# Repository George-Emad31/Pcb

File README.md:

# Pcb
course links

—-----------------------------------------------------------
An Introductory Session to the field & market by Eng. Marina & Abdelrahman
https://youtu.be/WNl0apc1B7U?si=2tqRJhkXzuk2Huat
—-----------------------------------------------------------
وليد عيسي
١- دورة الالكترونيات العملية 
https://youtube.com/playlist?list=PLww54WQ2wa5rOJ7FcXxi-CMNgmpybv7ei&si=CNx4IFHqYKsxTS9Y

٢- دورة الالكترونيات الرقمية 
https://youtube.com/playlist?list=PLww54WQ2wa5obq6IbRbIiql8oHaTUp3T_&si=EiO0YVdOyis6UTqZ

١- و ٢- ممكن تستبدلهم ب
(crash course electronics & PCB Design)
علي (Udemy) ل Andre Lamothe 👇

https://www.udemy.com/course/crash-course-electronics-and-pcb-design/?couponCode=SKILLS4SALEB

٣- دورة التصميم الالكتروني المحترف
https://youtube.com/playlist?list=PLww54WQ2wa5oKEhE_D3UVbKWwml8o8_Fu&si=GUjIskn36xYq0Vrd
 
٤- باور الكترونكس
https://youtube.com/playlist?list=PLa7G9a0g8LGJGPSlsJ-3jR8Icn2ZBpkbO&si=j0Y4SN-4wLoZTFAJ

٥-  في المختبر 
https://youtube.com/playlist?list=PLww54WQ2wa5oE2p9IJzItQwpLKtizHO_H&si=7gjoG86Fukzq-uNG

Dr.Mohamed Youssef (PCB Basics)
https://youtube.com/playlist?list=PLfgCIULRQavx6TjOhr_7pkx7ne4kI1r2N
Walid Balid (PCB Basics)
https://youtube.com/playlist?list=PL_UUr-UkFMWRXeJ2mKt5jidU5hId4-gwY&si=ZF-LGmuCmhe2fAAh

م.عمرو عباس (Altium)  
https://youtube.com/playlist?list=PLjAwsXyLubqXhIs1Xjf421pyehGvs9RpD&si=hDhPsAw99uElP_TQ

د.محمد الشامي  (Altium) 
https://youtube.com/playlist?list=PLZ42ZUInDWC5hSe0zNn84jiYI7bpQkXqb&si=qIUQ1LDYL5tfv7yA

Shawn Hymel (Kicad)
https://youtube.com/playlist?list=PL3bNyZYHcRSUhUXUt51W6nKvxx2ORvUQB&feature=shared

Parallel Systems EDA (OrCAD Allegro)
https://www.youtube.com/@parsysEDA/videos

Andre Lamothe (Embedded)
(Crash Course Arduino and Microcontroller Development)
https://www.udemy.com/course/crash-course-arduino-and-microcontroller-development/?couponCode=SKILLS4SALEB

Another Recommended good Embedded Course 
https://www.udemy.com/course/microcontrollers-sensors-actuators-recorded-by-arabic/?couponCode=SKILLS4SALEB
______________________________________

FastBit Embedded Brain Academy Embedded
https://www.udemy.com/user/kiran-nayak-2/?kw=Fastbit&src=sac

Robert Feranec     (YouTube channel + 3 paid courses)
https://www.youtube.com/@RobertFeranec

- learn to design your own board (Udemy)
- Advanced hardware design (fedevel academy)
- Advanced PCB layout (fedevel academy)
https://www.udemy.com/share/1029yK3@ESy1HsZxC51XGr01DA7xO2LyQJOntExK32Gf5kavSXH6ODqpkA5D4g6xnz0SwEeq7w==/

https://www.fedevel.com/courses

Phil's lab (YouTube channel + 2 paid courses)
https://www.youtube.com/@PhilsLab

- Mixed signal hardware design (fedevel academy)
- Advanced digital hardware design (fedevel academy)
https://www.fedevel.com/courses
______________________________________________________________________________
Eric Bogatin Academy
https://teledynelecroy.bethesignal.com/pages/24/signal-integrity-academy-be-the-signal

Altium Academy
https://www.youtube.com/@AltiumAcademy

EsteemPCB academy (YouTube + 4 Udemy courses)
https://www.youtube.com/@EsteemPCB
https://www.udemy.com/user/aviral-mishra-37/

STM32 IOT LTE Hardware Design course (Udemy)
https://www.udemy.com/course/stm32-internet-of-things-with-4g-lte-modem-hardware/

Hans Rosenberg (RF PCB Layout)
https://www.youtube.com/@HansRosenberg74
______________________________________________________________________________
RAHsoft courses (RF + Communication + Antenna)
https://www.udemy.com/user/rahsoft-rf-certificate/
https://www.udemy.com/user/security-and-cryptography-rahsoft-cyber-certificate/
______________________________________________________________________________
Kirsch Mackey (Hasofu Academy) 
https://youtube.com/@techedkirsch?si=i_7RqJdtHQidq5RQ

https://academy.hasofu.com/course/hardware-engineer-accelerator-videos-group
______________________________________________________________________________
Microchip University Courses 
https://mu.microchip.com/page/all-courses

Dario Fresu   (YouTube + Skool Academy website and application)  (Content related to EMC)
https://www.youtube.com/@dario_fresu
https://kp.odysee.tv/@fresudario:3?view=content
____________________________________________________________________________
Karen Burnham (EMC Basics)
https://www.udemy.com/course/emc-engineering-basics/?kw=emc+engineering&src=sac

Technologies Discussion (EMC course)
https://youtube.com/playlist?list=PLFxhgwM1F4ywicEggR3pzF0FcFcGQvZ82&si=Gw-rwGJun5NXbTx-

EMC Academy 
https://www.academyofemc.com/

Learn EMC
https://learnemc.com/

Keith Armstrong (EMC courses)
https://fedevel.com/instructors/keith-armstrong
_____________________________________________________________________
Ninedotconnects (High-Speed & Signal Integrity)
https://www.ninedotconnects.com/video-high-speed-design

Practical High-Speed Digital Design
https://www.udemy.com/course/practical-high-speed-digital-design/?couponCode=KEEPLEARNING
—-----------------------------------------------------------------------------------------------------------------------------
PCB/Electronics: Thermal Management, Cooling and Derating
https://www.udemy.com/course/pcbelectronics-thermal-management-derating-fundamentals/?kw=thermal+manag&src=sac&couponCode=KEEPLEARNING
—-------------------------------------------------------------------------------------------------------------------------
Battery Management Systems Specialization   (Coursera)
https://www.coursera.org/specializations/algorithms-for-battery-management-systems
BMS material by Colorado Boulder university
https://mocha-java.uccs.edu/ECE5720/index.html
http://mocha-java.uccs.edu/
BMS courses (Udemy)
https://www.udemy.com/user/ritul-shah/
—-----------------------------------------------------------
Microcontroller + Digital Control + Python for Power Electronics
https://www.udemy.com/user/shivkumar-iyer/
—-------------------------------------------------------------------------------------------------------------------------
- Power Electronics Specialization  (Coursera)
https://www.coursera.org/specializations/power-electronics

*MIT University Power Electronics Lectures*
Lectures
https://youtube.com/playlist?list=PLUl4u3cNGP62UTc77mJoubhDELSC8lfR0&si=k29GKX0zg4WzzoGR
Written, Quizzes 
https://ocw.mit.edu/courses/6-622-power-electronics-spring-2023/pages/syllabus/
—-----------------------------------------------------------------------------------------------------------------------------
Flyback Converter Design
https://www.youtube.com/@electrokickoff/playlists
—-----------------------------------------------------------------------------------------------------------------------------
AC/DC-DC Converters course by Eng.Islam Saeed
https://youtu.be/kJaOMY92Ivg?si=VJFJQ_Acn8bhjlOw
https://www.linkedin.com/posts/islamsaeedrej_smps-design-course-online-activity-7283790675265867777-NSWV?utm_source=share&utm_medium=member_desktop&rcm=ACoAAC2EX84B1PiRTD7OQLJM88wBkoDjDiXYB1M

HW Engineer to the Market course by Eng.Islam Saeed
https://www.linkedin.com/posts/islamsaeedrej_hwabrengineerabrtoabrmarket-hw-electronics-activity-7241157567031222272-e6iD?utm_source=share&utm_medium=member_desktop&rcm=ACoAAC2EX84B1PiRTD7OQLJM88wBkoDjDiXYB1M

Eng.Fahd Fakhry (3 Udemy Courses)
- Voltage control DC-DC Converters
- Current control DC-DC Converters
- Motor Control
https://www.udemy.com/user/fahd-fakhry/
  
Sam Ben Yaakov
https://youtube.com/@sambenyaakov?si=wgDwYokDsXTC1p-A

LTspice Simulator
https://youtube.com/playlist?list=PLT84nve2j1g_wgGcm0Bv3K4RSl2Jdjsey&si=4YQyyxi4m5Yk-7JN
https://www.youtube.com/@MarcosAlonsoElectronics
https://www.udemy.com/course/ltspice-tutorial-for-beginners/?srsltid=AfmBOopKCXsha7NvuIdynjStsrGotg1k3i8vl-c6bjZIeW8euqYZ-T-9&couponCode=KEEPLEARNING
-Springer book is very detailed & suitable for beginners (In books folder)

Hardware Design Diploma by Eng. Mahmoud Arafa 
https://www.linkedin.com/posts/mahmoud-arafa-63b1531a2_%D9%88%D9%85%D8%A7-%D8%A3%D9%88%D8%AA%D9%8A%D8%AA%D9%85-%D9%85%D9%86-%D8%A7%D9%84%D8%B9%D9%84%D9%85-%D8%A5%D9%84%D8%A7-activity-7301257242983444480-LV6l?utm_source=share&utm_medium=member_android&rcm=ACoAAC2EX84B1PiRTD7OQLJM88wBkoDjDiXYB1M
—-----------------------------------------------------------------------------------------------------------------------------
FPGA & ASIC & Digital Design Roadmap+Courses

https://github.com/m3y54m/FPGA-ASIC-Roadmap
https://docs.google.com/document/d/10o4X9itOy4x89zeV04_ipY3Gark36JPEXNdBuAvmYeo/edit?usp=drivesdk

https://www.coursera.org/specializations/fpga-design

https://www.udemy.com/course/learn-fpga-design-with-vhdl/?couponCode=KEEPLEARNING

https://www.udemy.com/user/scott-dickson-24/
—-----------------------------------------------------------------------------------------------------------------------------

Valuable Youtube Channels/Webinars

(Rick Hartley) (Grounding)
https://www.youtube.com/live/ySuUZEjARPY?si=bUzMwo6jEBJyy3bA
Kenneth Wyatt (EMC)
https://youtu.be/Krz2Ylj1ZL0?si=EmpSjO_qbGCL12Qk

(Switching Power Supply PCB Layout seminar)
https://www.youtube.com/watch?v=gq-0ZpcGm8E&list=PL5HT7zybEW4T6YcbzQNgPOsIHYw9Rx3MO&index=1&t=1s

https://youtube.com/@electronicmindsuk?si=DOjJMiWhiH3QeP5y

https://www.youtube.com/@DeepBlueMbedded/video

https://www.youtube.com/watch?v=Rgaq5ax71fE&t=1924s

https://youtu.be/cp7II9eqrRU?si=URyDxuNK9eS4KUwh

https://youtube.com/@protoexpresspcb?si=lShLU8rDZzs9lSuV

https://www.youtube.com/live/ySuUZEjARPY?si=1zLlpm-SNm39GcgB

https://www.youtube.com/@electrokickoff

https://www.youtube.com/@AbdelrahmanFarghly/videos

https://www.youtube.com/@mehdiferdowsi9085/videos

https://youtube.com/@techedkirschee?si=Nm_miLClPOZQhHhi

https://youtube.com/@myvanitar?si=56ywRsskvA4lR-qZ

https://www.youtube.com/@EEVblog

https://www.youtube.com/@ELECTRONOOBS

https://www.youtube.com/@greatscottlab

https://www.youtube.com/@BenEater

https://youtube.com/@allaboutelectronics?si=6oBa0x1gGjo1Kh3a

https://www.youtube.com/@0033mer

https://youtube.com/@pcbafrica?si=ll_wLASnqxahkNoS

https://youtube.com/@wuerthelektronikindia-syst5575?si=KUmm86rngWClG2IF

https://youtube.com/@birichalectures?si=rNIujXQz3ECKQT6f

https://youtube.com/@machonedesignemc?si=mH5KCG_DfA04g-Ms

https://youtube.com/@rohde-schwarz?si=MPC_WLR9FluGZkrc

https://youtube.com/@brianbdouglas?si=jIRKR843M4sZlig2

https://youtu.be/HTywk_tlcAk?si=R28jWKTjXR82VGE_

https://www.youtube.com/@pantechelearning

https://youtube.com/@manoa98a?si=2GIbcFX2UrzrGINO

https://youtube.com/@electrobuff?si=7wJEBCNmq7W81LR6

https://youtube.com/@electronicscircuithubech?si=H3kTSfEw0ztwP0nA

https://youtube.com/@technologiesdiscussion1676?si=lvN-GNv7xp8e9dRu

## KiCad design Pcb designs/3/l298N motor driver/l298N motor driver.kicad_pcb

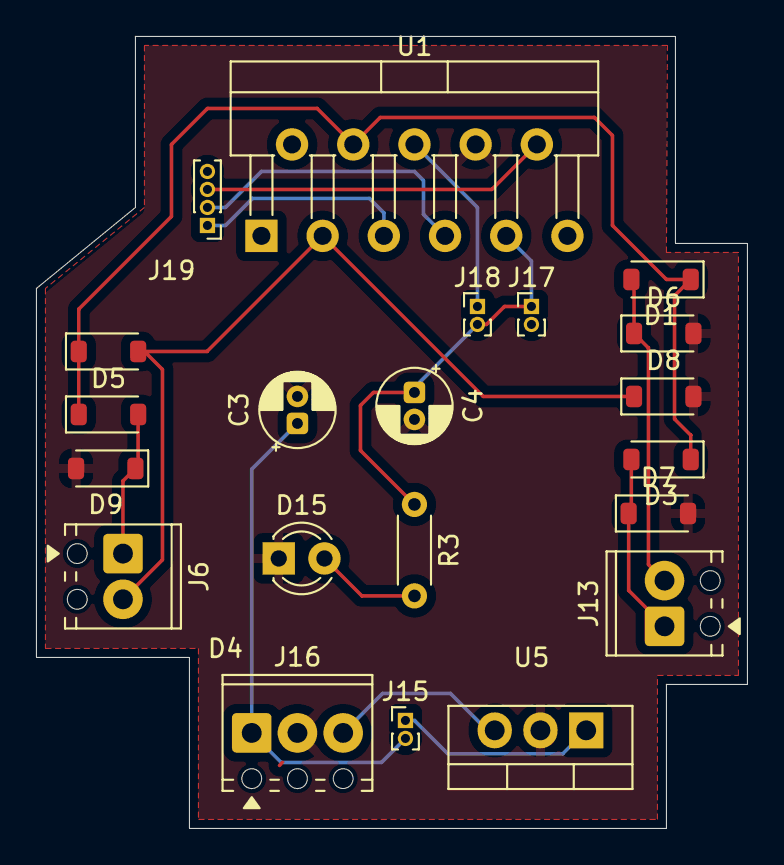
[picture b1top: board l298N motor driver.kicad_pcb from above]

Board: 2 copper layers, 39.5 x 44.0 mm, 21 parts (0 on the bottom side), 15 nets.

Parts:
C3, C4: C_Polarized_Small; CP_Radial_D4.0mm_P1.50mm
D1, D3, D4, D5, D6, D7, D8, D9: BAV16W; D_SOD-123
D15: LED; LED_D3.0mm
J6, J13: Screw_Terminal_01x02; TerminalBlock_Phoenix_MPT-0,5-2-2.54_1x02_P2.54mm_Horizontal
J15, J17, J18: Conn_01x02_Pin; PinHeader_1x02_P1.00mm_Vertical
J16: Screw_Terminal_01x03; TerminalBlock_Phoenix_MPT-0,5-3-2.54_1x03_P2.54mm_Horizontal
J19: Conn_01x04_Pin; PinHeader_1x04_P1.00mm_Vertical
R3: R; R_Axial_DIN0204_L3.6mm_D1.6mm_P5.08mm_Horizontal
U1: L298HN; TO-220-11_P3.4x5.08mm_StaggerOdd_Lead4.58mm_Vertical
U5: LM7805_TO220; TO-220-3_Vertical

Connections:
5V: C4.1, J16.3, J17.1, J18.2, R3.1, U1.9 (Vss), U5.3 (VO)
GND: C3.2, C4.2, D6.2 (A), D7.2 (A), D8.2 (A), D9.2 (A), D15.1 (K), J16.2, U1.8 (GND), U5.2 (GND)
unnamed: D1.2 (A), D6.1 (K), J13.2
unnamed: D3.2 (A), D7.1 (K), J13.1
unnamed: D4.2 (A), D8.1 (K), J6.2, U1.3 (OUT2)
unnamed: D5.2 (A), D9.1 (K), J6.1, U1.2 (OUT1)
unnamed: D15.2 (A), R3.2
unnamed: J15.1, U5.1 (VI)
unnamed: C3.1, J15.2, J16.1
unnamed: J17.2, U1.11 (EnB)
unnamed: J18.1, U1.6 (EnA)
unnamed: J19.1, U1.5 (IN1)
unnamed: J19.2, U1.7 (IN2)
unnamed: J19.3, U1.10 (IN3)
PWR_INPUT: D1.1 (K), D3.1 (K), D4.1 (K), D5.1 (K), U1.4 (Vs)

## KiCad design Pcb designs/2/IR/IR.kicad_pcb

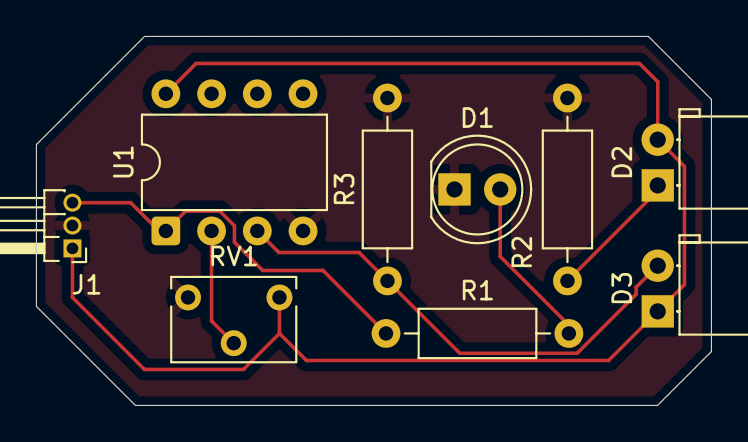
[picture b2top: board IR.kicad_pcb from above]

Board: 2 copper layers, 37.5 x 20.5 mm, 9 parts (0 on the bottom side), 7 nets.

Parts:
D1: LED; LED_D5.0mm_Clear
D2: ir; LED_D5.0mm_Horizontal_O1.27mm_Z3.0mm_IRGrey
D3: photo diod; LED_D5.0mm_Horizontal_O1.27mm_Z3.0mm_IRBlack
J1: Conn_01x03_Pin; PinHeader_1x03_P1.27mm_Horizontal
R1, R2, R3: R; R_Axial_DIN0207_L6.3mm_D2.5mm_P10.16mm_Horizontal
RV1: R_Potentiometer; Potentiometer_Bourns_3266W_Vertical
U1: LM358; DIP-8_W7.62mm

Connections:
GND: D1.1 (K), J1.2, R2.2, R3.2, RV1.3, U1.4 (V-)
unnamed: D1.2 (A), R1.2
unnamed: D2.1 (K), R2.1
unnamed: D3.2 (A), R3.1, U1.3 (+)
unnamed: RV1.2, U1.2 (-)
OUT: J1.3, R1.1, U1.1
VCC: D2.2 (A), D3.1 (K), J1.1, RV1.1, U1.8 (V+)

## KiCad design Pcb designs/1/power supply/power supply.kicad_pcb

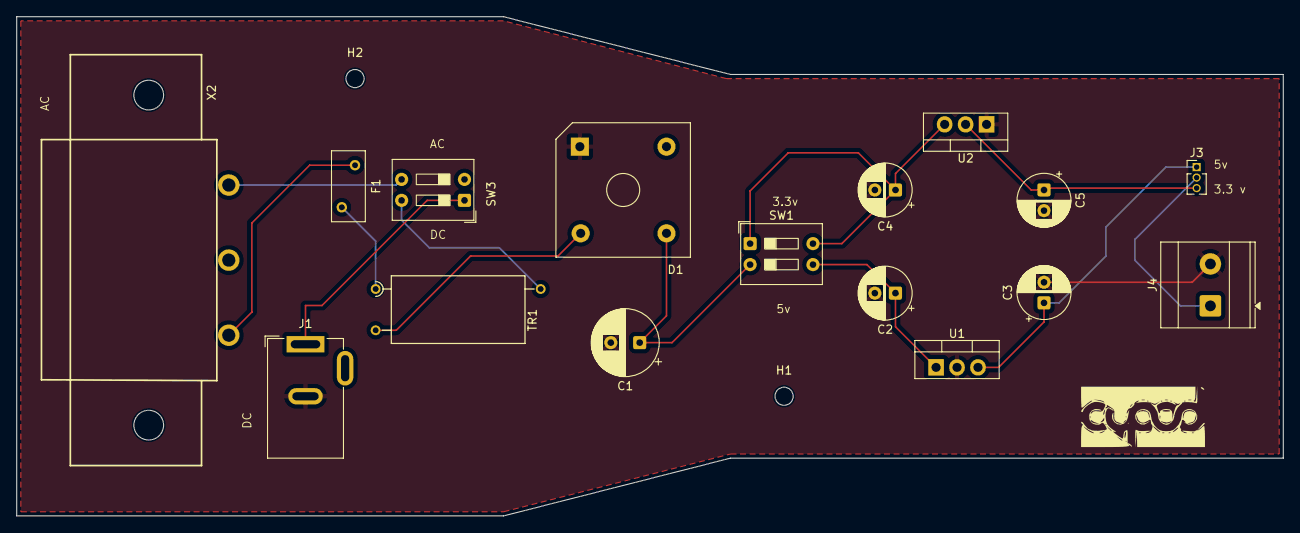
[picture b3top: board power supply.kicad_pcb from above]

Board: 2 copper layers, 153.5 x 60.5 mm, 18 parts (0 on the bottom side), 13 nets.

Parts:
C1: 1000uf; CP_Radial_D8.0mm_P3.50mm
C2, C3, C4, C5: 10uf; CP_Radial_D6.3mm_P2.50mm
D1: VS-KBPC104; Diode_Bridge_Vishay_KBPC1
F1: Fuse; Fuse_BelFuse_0ZRE0005FF_L8.3mm_W3.8mm
H1, H2: MountingHole; MountingHole_2.2mm_M2
J1: Jack-DC; BarrelJack_GCT_DCJ200-10-A_Horizontal
J3: Conn_01x03_Pin; PinHeader_1x03_P1.27mm_Vertical
J4: Screw_Terminal_01x02; TerminalBlock_Phoenix_MKDS-3-2-5.08_1x02_P5.08mm_Horizontal
SW1: SW_Push_DPDT; SW_DIP_SPSTx02_Slide_9.78x7.26mm_W7.62mm_P2.54mm
SW3: SW_DPST; SW_DIP_SPSTx02_Slide_9.78x7.26mm_W7.62mm_P2.54mm
TR1: TRANSF1; Autotransformer_ZS1052-AC
U1: LM7805_TO220; TO-220-3_Vertical
U2: AMS1117-3.3; TO-220-3_Vertical
X2: 6ESRM-P

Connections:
/3.3v: C5.1, J3.3, U2.2 (VO)
/5v: C3.1, J3.1, U1.3 (VO)
GND: C1.2, C2.2, C3.2, C4.2, C5.2, D1.1 (+), J1.2, J4.2, U1.2 (GND), U2.1 (GND)
IN_1: C4.1, SW1.1 (A), SW1.4 (A), U2.3 (VI)
IN_2: C2.1, SW1.3 (C), U1.1 (VI)
unnamed: C1.1, D1.3 (-), SW1.2 (B)
unnamed: D1.2, TR1.3
unnamed: F1.1, X2.3
unnamed: F1.2, TR1.1
unnamed: J1.1, SW3.1
unnamed: J3.2, J4.1
unnamed: SW3.3, X2.1
unnamed: SW3.4, TR1.2

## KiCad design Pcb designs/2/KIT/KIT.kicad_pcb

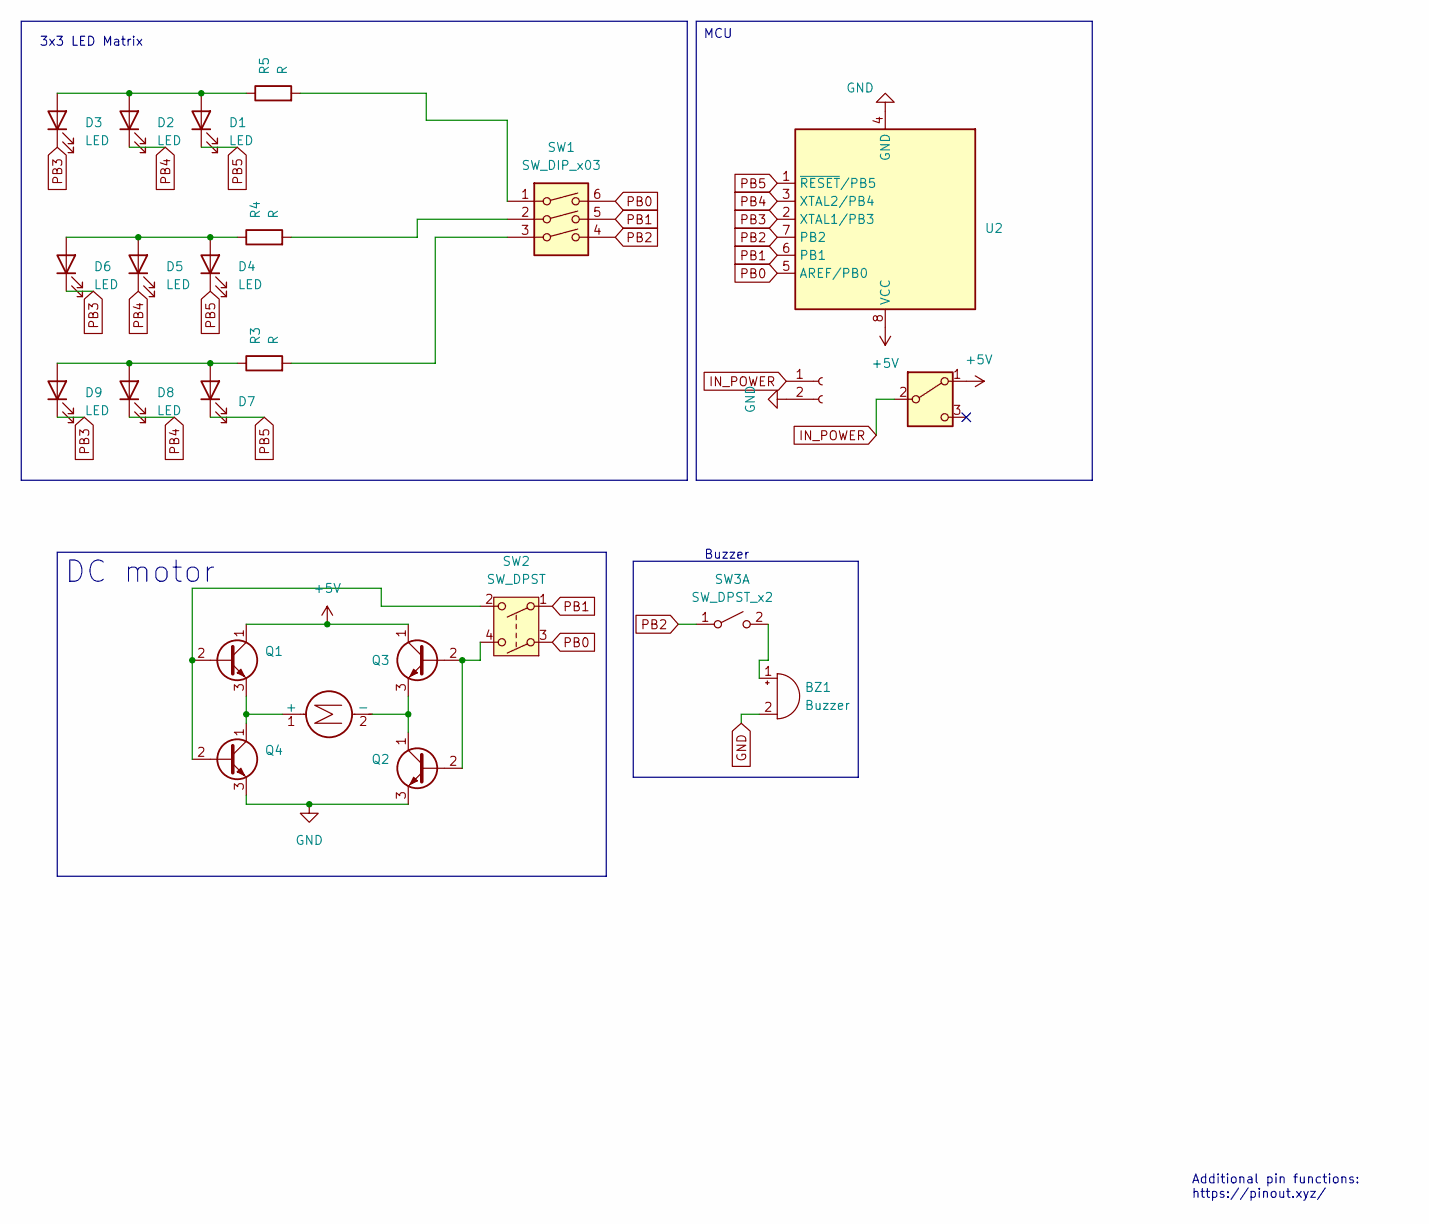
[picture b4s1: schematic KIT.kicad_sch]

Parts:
BZ1: Buzzer; MagneticBuzzer_ProSignal_ABT-410-RC
D1, D2, D3, D4, D5, D6, D7, D8, D9: LED; LED_D5.0mm_Clear
J1: Conn_01x02_Socket; TerminalBlock_Phoenix_PT-1,5-2-3.5-H_1x02_P3.50mm_Horizontal
M1: Motor_DC; PinHeader_1x02_P1.27mm_Vertical
Q1, Q2, Q3, Q4: BC547; TO-92_Inline
R3, R4, R5: R; R_Axial_DIN0204_L3.6mm_D1.6mm_P5.08mm_Horizontal
SW1: SW_DIP_x03; SW_DIP_SPSTx03_Slide_Copal_CVS-03xB_W5.9mm_P1mm
SW2: SW_DPST; SW_DIP_SPSTx02_Slide_6.7x6.64mm_W7.62mm_P2.54mm_LowProfile
SW3: SW_DPST_x2; SW_DIP_SPSTx01_Piano_10.8x4.1mm_W7.62mm_P2.54mm
SW4: SW_DPDT_x2; SW_DIP_SPSTx02_Piano_10.8x6.64mm_W7.62mm_P2.54mm
U2: ATtiny45-20P; DIP-8_W7.62mm

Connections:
+5V: Q1.1 (C), Q3.1 (C), SW4.1 (A), U2.8 (VCC)
GND: BZ1.2 (-), J1.2, Q2.3 (E), Q4.3 (E), U2.4 (GND)
IN_POWER: J1.1, SW4.2 (B)
unnamed: BZ1.1 (+), SW3.2 (B)
unnamed: D1.2 (A), D2.2 (A), D3.2 (A), R5.1
unnamed: D4.2 (A), D5.2 (A), D6.2 (A), R4.1
unnamed: D7.2 (A), D8.2 (A), D9.2 (A), R3.1
unnamed: M1.1 (+), Q1.3 (E), Q4.1 (C)
unnamed: M1.2 (-), Q2.1 (C), Q3.3 (E)
unnamed: Q1.2 (B), Q4.2 (B), SW2.2
unnamed: Q2.2 (B), Q3.2 (B), SW2.4
unnamed: R3.2, SW1.3
unnamed: R4.2, SW1.2
unnamed: R5.2, SW1.1
PB0: SW1.6, SW2.3, U2.5 (AREF/PB0)
PB1: SW1.5, SW2.1, U2.6 (PB1)
PB2: SW1.4, SW3.1 (A), U2.7 (PB2)
PB3: D3.1 (K), D6.1 (K), D9.1 (K), U2.2 (XTAL1/PB3)
PB4: D2.1 (K), D5.1 (K), D8.1 (K), U2.3 (XTAL2/PB4)
PB5: D1.1 (K), D4.1 (K), D7.1 (K), U2.1 (~RESET/PB5)

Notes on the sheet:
Buzzer
3x3 LED Matrix
Additional pin functions: https://pinout.xyz/
MCU
DC motor

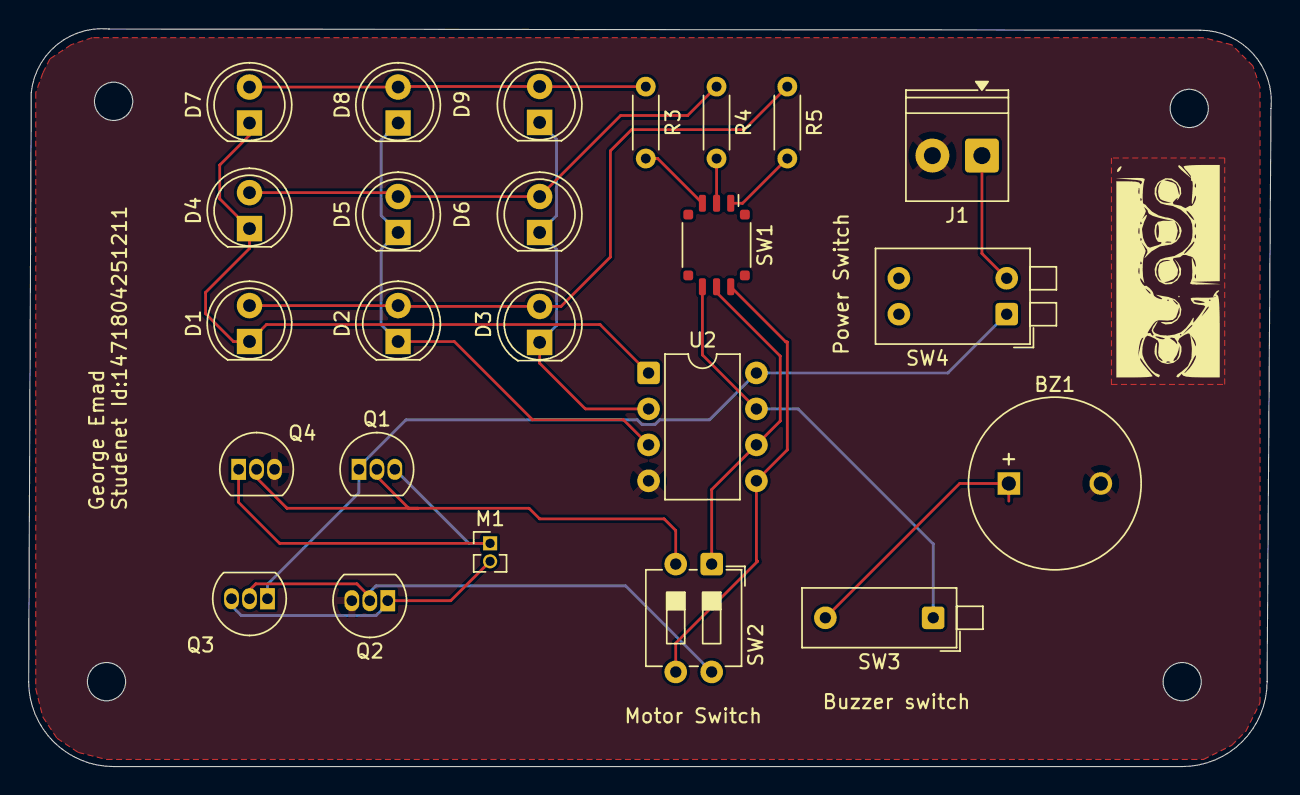
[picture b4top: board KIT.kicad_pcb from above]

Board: 2 copper layers, 87.8 x 52.1 mm, 28 parts (0 on the bottom side), 20 nets.

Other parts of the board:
MH1, MH2, MH3, MH4: MountingHole_2.7mm_M2.5

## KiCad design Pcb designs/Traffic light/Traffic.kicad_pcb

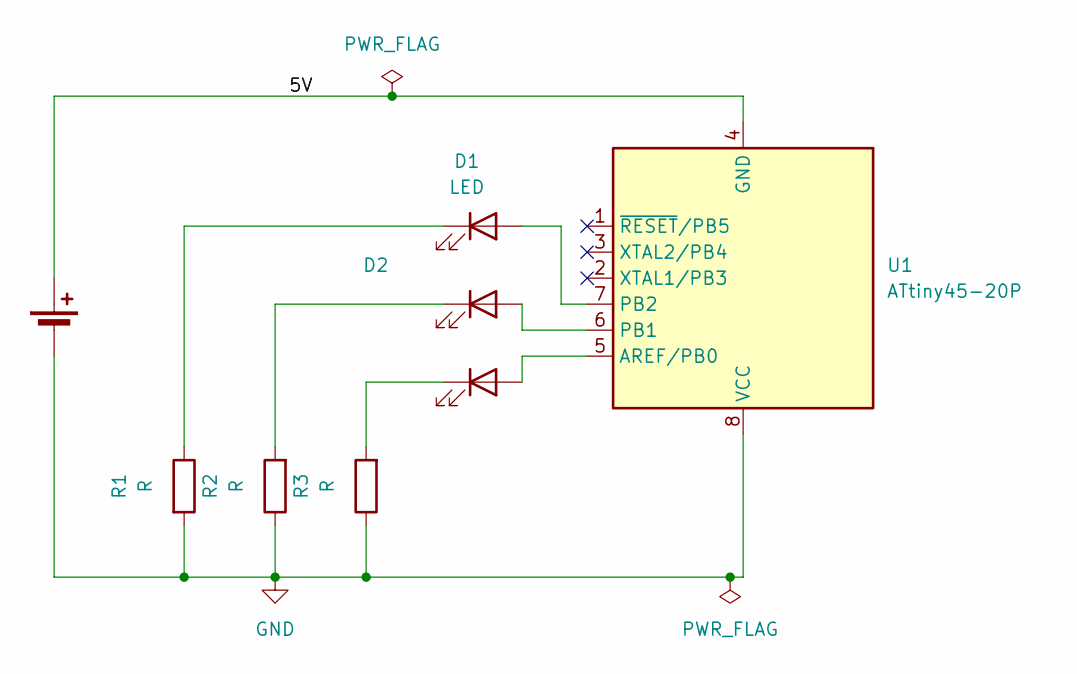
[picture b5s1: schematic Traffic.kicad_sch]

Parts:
BT1: Battery_Cell; BatteryHolder_Keystone_1060_1x2032
D1, D2, D3: LED; LED_D3.0mm
R1, R2, R3: R; R_Axial_DIN0204_L3.6mm_D1.6mm_P2.54mm_Vertical
U1: ATtiny45-20P; DIP-8_W7.62mm

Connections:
/5V: BT1.1 (+), U1.4 (GND)
GND: BT1.2 (-), R1.2, R2.1, R3.1, U1.8 (VCC)
unnamed: D1.2 (A), U1.7 (PB2)
unnamed: D1.1 (K), R1.1
unnamed: D2.2 (A), U1.6 (PB1)
unnamed: D2.1 (K), R2.2
unnamed: D3.2 (A), U1.5 (AREF/PB0)
unnamed: D3.1 (K), R3.2

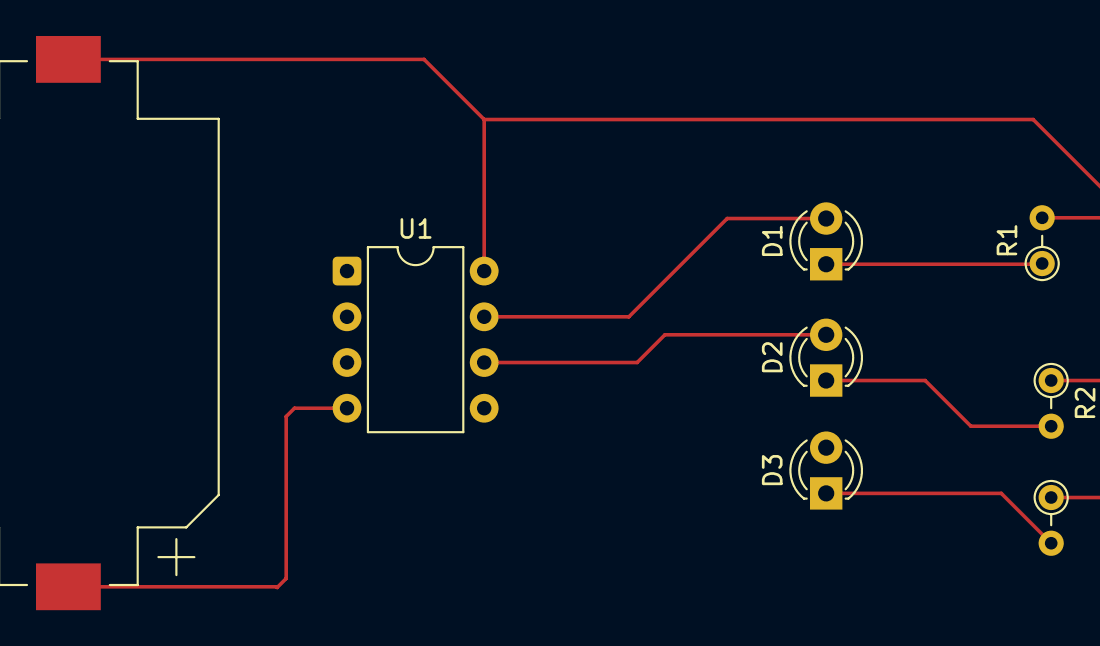
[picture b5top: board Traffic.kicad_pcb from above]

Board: 2 copper layers, 8 parts (0 on the bottom side), 8 nets.

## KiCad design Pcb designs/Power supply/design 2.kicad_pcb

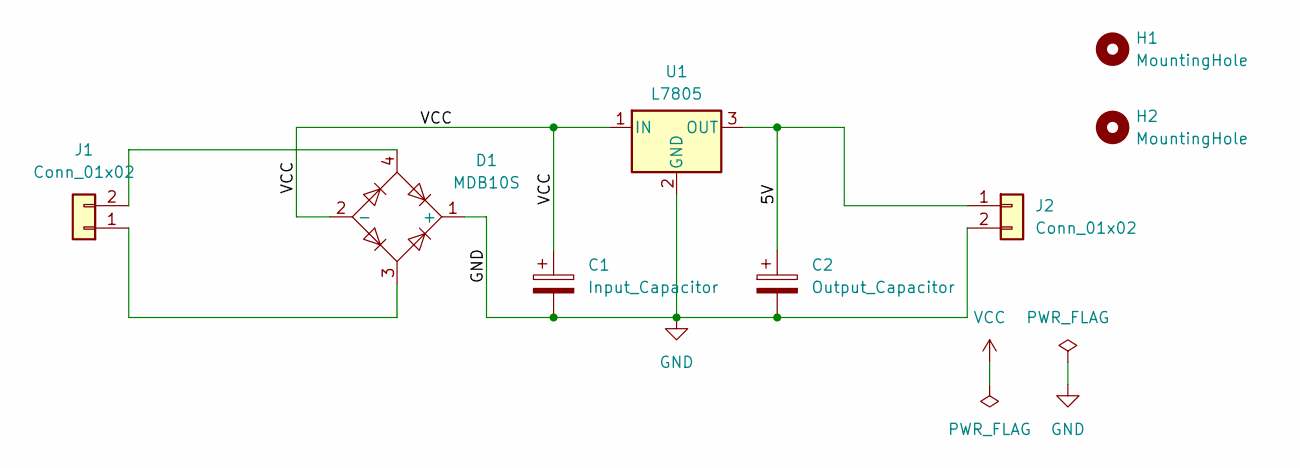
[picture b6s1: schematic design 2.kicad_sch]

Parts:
C1: Input_Capacitor; CP_Radial_D5.0mm_P2.00mm
C2: Output_Capacitor; CP_Radial_D5.0mm_P2.00mm
D1: MDB10S; TSSOP-4_4.4x5mm_P4mm
H1, H2: MountingHole; MountingHole_2.2mm_M2_DIN965_Pad
J1, J2: Conn_01x02; TerminalBlock_Phoenix_MKDS-1,5-2_1x02_P5.00mm_Horizontal
U1: L7805; TO-220-3_Vertical

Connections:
/5V: C2.1, J2.1, U1.3 (OUT)
GND: C1.2, C2.2, D1.1 (+), J2.2, U1.2 (GND)
unnamed: D1.3, J1.1
unnamed: D1.4, J1.2
VCC: C1.1, D1.2 (-), U1.1 (IN)

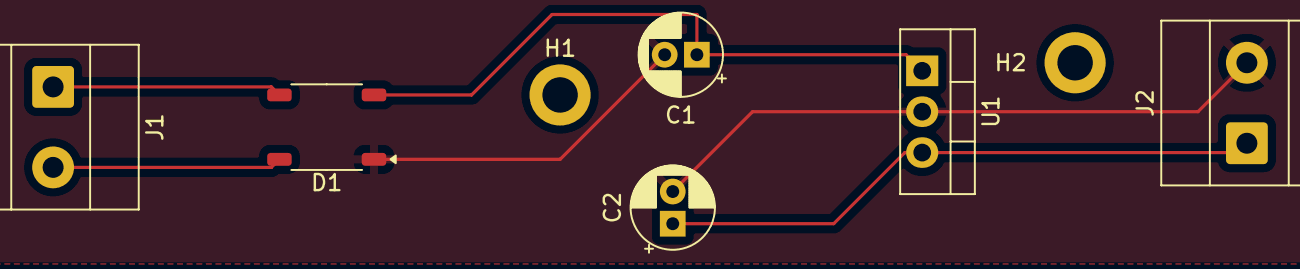
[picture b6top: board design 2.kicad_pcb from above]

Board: 2 copper layers, 8 parts (0 on the bottom side), 5 nets.

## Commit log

2025-04-28 Add files via upload
    Pcb design
2025-06-08 assignment 1,2,3
